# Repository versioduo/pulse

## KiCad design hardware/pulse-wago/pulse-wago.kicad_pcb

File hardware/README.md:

# V2 pulse

🧲 16 Channel Intelligent Solenoid Controller

## Schematic
[PDF](pulse/pulse.pdf)

## Bill Of Materials
[Interactive BOM](https://versioduo.com/view?url=https://raw.githubusercontent.com/versioduo/pulse/refs/heads/main/hardware/pulse/pulse-bom.html)

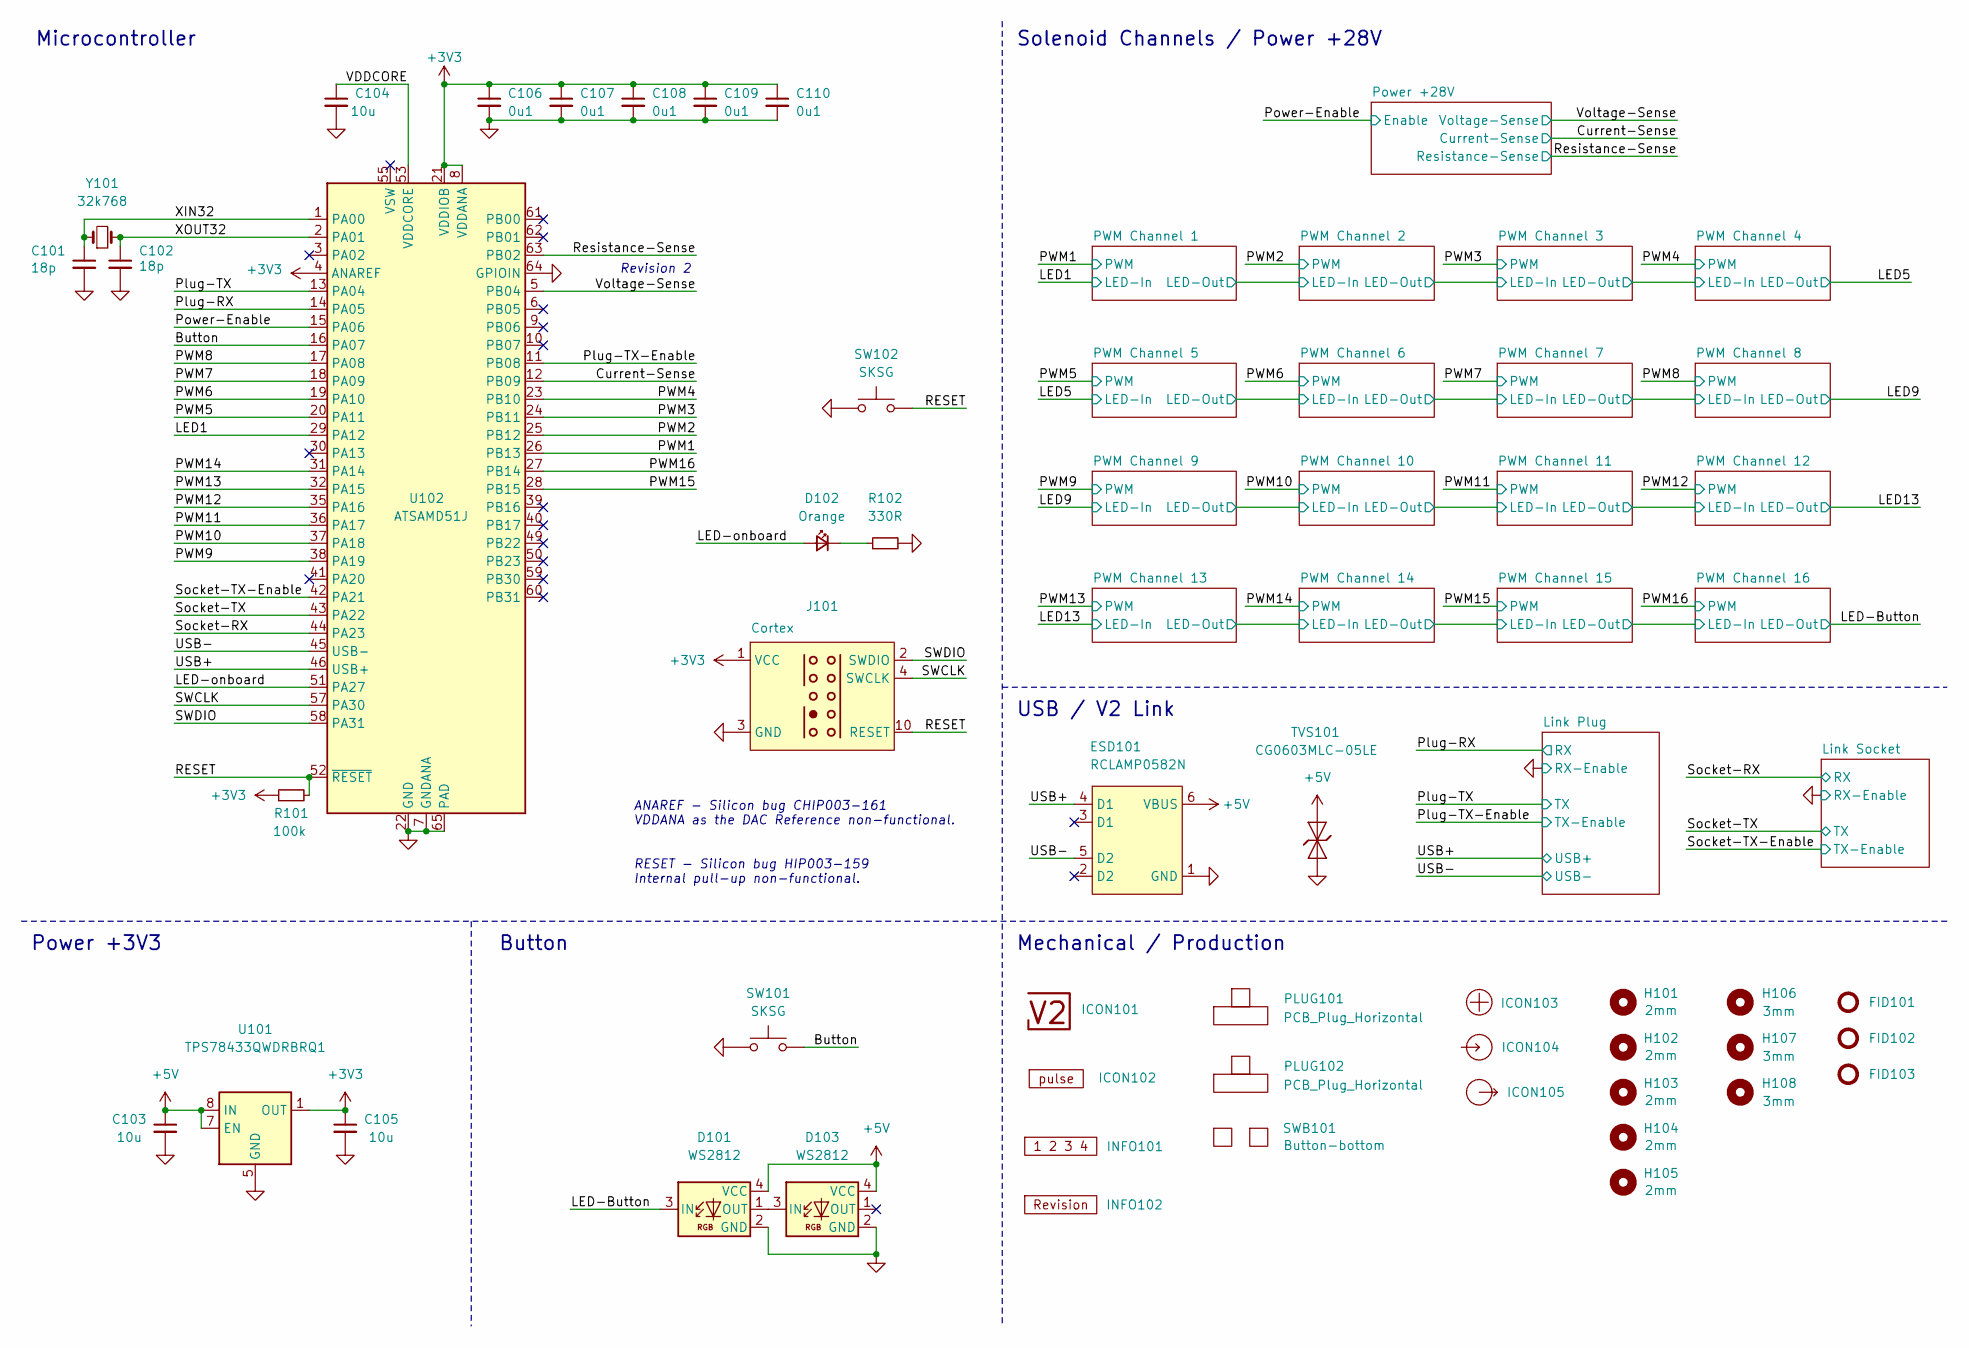
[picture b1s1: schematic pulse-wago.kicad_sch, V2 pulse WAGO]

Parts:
C101, C102: 18p; C_1608; Rating 50V; Mouser 810-CGA3E2C0G1H180J
C103, C105: 10u; C_2012; Rating 25V; Mouser 810-C2012X5R1E106K
C104: 10u; C_1608; Rating 10V; Mouser 810-C1608X6S1A106M
C106, C107, C108, C109, C110: 0u1; C_1608; Rating 50V; Mouser 810-CGA3E2X7R1H104MA
D101, D103: WS2812; WS2812-2020; Rating 15mA; LCSC C965555
D102: Orange; LED_1608; Rating 605nm; Mouser 755-SML-D12D1WT86
ESD101: RCLAMP0582N; SLP1210N6; Rating 20kV; Mouser 947-RCLAMP0582N.TCT
FID101, FID102, FID103: Fiducial_Paste; Fiducial_0.5mm_Mask1mm_Paste
H101, H102, H103, H104, H105: 2mm; MountingHole_2mm
H106, H107, H108: 3mm; MountingHole_3mm
ICON101: V2-logo; Logo_Small
ICON102: Board_pulse; Board_pulse_Small
ICON103: Plus; Plus_Small
ICON104: Arrow_In
ICON105: Arrow_Out
INFO101: Layer_Numbers-6
INFO102: Revision
J101: Cortex
PLUG101, PLUG102: PCB_Plug_Horizontal
R101: 100k; R_1608; Rating 100mW; Mouser 71-CRCW0603100KFKEAC
R102: 330R; R_1608; Rating 100mW; Mouser 71-CRCW0603330RFKEAC
SW101, SW102: SKSG; Rating 1.6N; Mouser 688-SKSGACE010
SWB101: Button-bottom; PCB_Button-bottom
TVS101: CG0603MLC-05LE; D_1608; Rating 5V; Mouser 652-CG0603MLC-05LE
U101: TPS78433QWDRBRQ1; VSON-8-1_3x3mm_P0.65_EP1.65x2.4mm; Rating 300mA; Mouser 595-TPS78433QWDRBRQ1
U102: ATSAMD51J; QFN-64-1EP_9x9mm_P0.5mm_EP4.8x4.8mm_ThermalVias; Rating Cortex-M4F; Mouser 556-ATSAMD51J19AMU
Y101: 32k768; Crystal_SMD_3215-2Pin_3.2x1.5mm; Rating 10ppm; Mouser 815-ABS0716632.768KT

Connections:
+3V3: C105.1, C106.1, C107.1, C108.1, C109.1, C110.1, J101.1 (VCC), R101.1, U101.1 (OUT), U102.4 (ANAREF), U102.8 (VDDANA), U102.21 (VDDIOB), U102.34 (VDDIO), U102.48 (VDDIO), U102.56 (VDDIO); also elsewhere on the board
+5V: C103.1, D101.4 (VCC), D103.4 (VCC), ESD101.6 (VBUS), TVS101.2 (A), U101.6 (EN), U101.7 (EN), U101.8 (IN); also elsewhere on the board
/Button: SW101.2, U102.16 (PA07)
/Current-Sense: U102.12 (PB09); also elsewhere on the board
/LED1: U102.29 (PA12); also elsewhere on the board
/LED-Button: D101.3 (IN); also elsewhere on the board
/LED-onboard: D102.2 (A), U102.51 (PA27)
/PWM1: U102.26 (PB13); also elsewhere on the board
/PWM2: U102.25 (PB12); also elsewhere on the board
/PWM3: U102.24 (PB11); also elsewhere on the board
/PWM4: U102.23 (PB10); also elsewhere on the board
/PWM5: U102.20 (PA11); also elsewhere on the board
/PWM6: U102.19 (PA10); also elsewhere on the board
/PWM7: U102.18 (PA09); also elsewhere on the board
/PWM8: U102.17 (PA08); also elsewhere on the board
/PWM9: U102.38 (PA19); also elsewhere on the board
/PWM10: U102.37 (PA18); also elsewhere on the board
/PWM11: U102.36 (PA17); also elsewhere on the board
/PWM12: U102.35 (PA16); also elsewhere on the board
/PWM13: U102.32 (PA15); also elsewhere on the board
/PWM14: U102.31 (PA14); also elsewhere on the board
/PWM15: U102.28 (PB15); also elsewhere on the board
/PWM16: U102.27 (PB14); also elsewhere on the board
/Plug-RX: U102.14 (PA05); also elsewhere on the board
/Plug-TX: U102.13 (PA04); also elsewhere on the board
/Plug-TX-Enable: U102.11 (PB08); also elsewhere on the board
/Power-Enable: U102.15 (PA06); also elsewhere on the board
/RESET: J101.10 (RESET), R101.2, SW102.2, U102.52 (~RESET)
/Resistance-Sense: U102.63 (PB02); also elsewhere on the board
/SWCLK: J101.4 (SWCLK), U102.57 (PA30)
/SWDIO: J101.2 (SWDIO), U102.58 (PA31)
/Socket-RX: U102.44 (PA23); also elsewhere on the board
/Socket-TX: U102.43 (PA22); also elsewhere on the board
/Socket-TX-Enable: U102.42 (PA21); also elsewhere on the board
/USB+: ESD101.4 (D1), U102.46 (USB+); also elsewhere on the board
/USB-: ESD101.5 (D2), U102.45 (USB-); also elsewhere on the board
/VDDCORE: C104.1, U102.53 (VDDCORE)
/Voltage-Sense: U102.5 (PB04); also elsewhere on the board
/XIN32: C101.1, U102.1 (PA00), Y101.1
/XOUT32: C102.1, U102.2 (PA01), Y101.2
GND: C101.2, C102.2, C103.2, C104.2, C105.2, C106.2, C107.2, C108.2, C109.2, C110.2, D101.2 (GND), D103.2 (GND), ESD101.1 (GND), J101.3 (GND), J101.5 (GND), R102.2, SW101.1, SW102.1, TVS101.1 (K), U101.5 (GND), U101.9 (GND), U102.7 (GNDANA), U102.22 (GND), U102.33 (GND), U102.47 (GND), U102.54 (GND), U102.64 (GPIOIN), U102.65 (PAD); also elsewhere on the board
unnamed: D101.1 (OUT), D103.3 (IN)
unnamed: D102.1 (K), R102.1

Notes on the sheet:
﻿ANAREF - Silicon bug CHIP003-161 VDDANA as the DAC Reference non-functional.
Solenoid Channels / Power +28V
RESET - ﻿Silicon bug HIP003-159 Internal pull-up non-functional.
Button
Revision 2
USB / V2 Link
Mechanical / Production
Power +3V3
Microcontroller

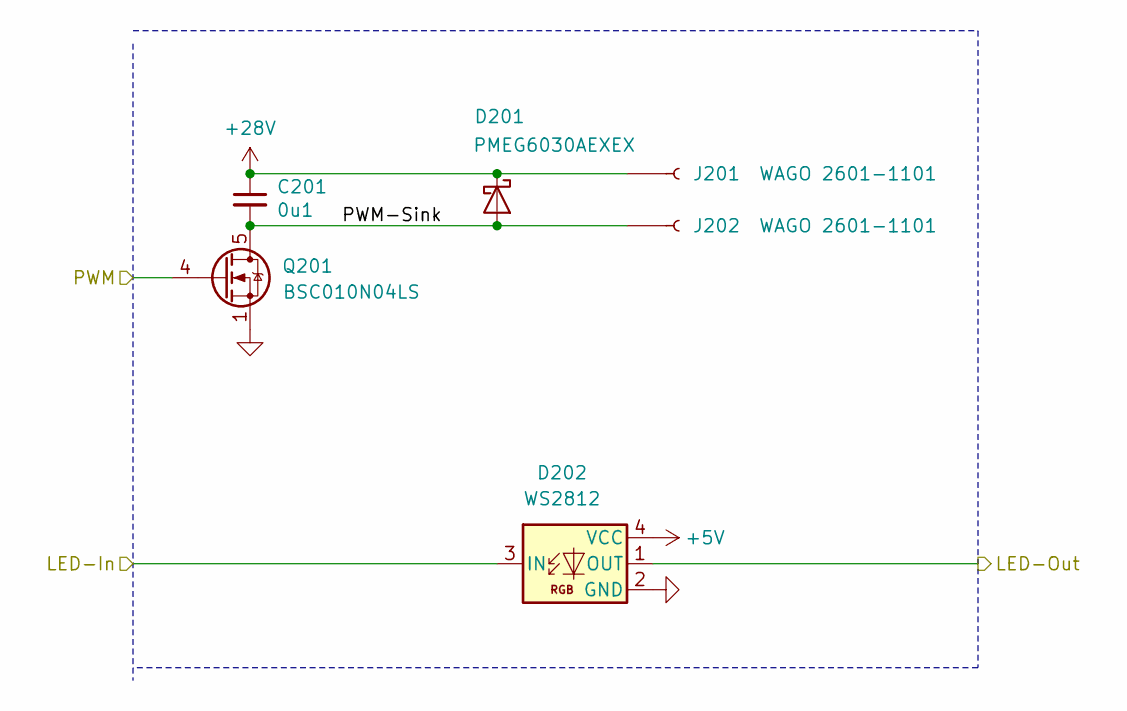
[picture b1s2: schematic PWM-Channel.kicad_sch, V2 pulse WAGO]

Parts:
C201: 0u1; C_1608; Rating 50V; Mouser 810-CGA3E2X7R1H104MA
D201: PMEG6030AEXEX; D_SOD-123HP; Rating 60V; Mouser 771-PMEG6030AEXEX
D202: WS2812; WS2812-2020; Rating 15mA; LCSC C965555
J201, J202: WAGO 2601-1101; 2601-1101; Rating 17.5A
Q201: BSC010N04LS; TDSON-8-FL; Rating 40V; Mouser 726-BSC010N04LS

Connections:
+5V: D202.4 (VCC); also elsewhere on the board
+28V: C201.1, D201.1 (K), J201.1; also elsewhere on the board
/LED1: D202.3 (IN); also elsewhere on the board
/PWM1: Q201.4 (G); also elsewhere on the board
/PWM Channel 1/LED-Out: D202.1 (OUT); also elsewhere on the board
/PWM Channel 1/PWM-Sink: C201.2, D201.2 (A), J202.1, Q201.5 (D)
GND: D202.2 (GND), Q201.1 (S); also elsewhere on the board

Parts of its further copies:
C301, C401, C501, C601, C701, C801, C901, C1001, C1101, C1201, C1301, C1401, C1501, C1601, C1701: 0u1; C_1608; Rating 50V; Mouser 810-CGA3E2X7R1H104MA
D301, D401, D501, D601, D701, D801, D901, D1001, D1101, D1201, D1301, D1401, D1501, D1601, D1701: PMEG6030AEXEX; D_SOD-123HP; Rating 60V; Mouser 771-PMEG6030AEXEX
D302, D402, D502, D602, D702, D802, D902, D1002, D1102, D1202, D1302, D1402, D1502, D1602, D1702: WS2812; WS2812-2020; Rating 15mA; LCSC C965555
J301, J302, J401, J402, J501, J502, J601, J602, J701, J702, J801, J802, J901, J902, J1001, J1002, J1101, J1102, J1201, J1202, J1301, J1302, J1401, J1402, J1501, J1502, J1601, J1602, J1701, J1702: WAGO 2601-1101; 2601-1101; Rating 17.5A
Q301, Q401, Q501, Q601, Q701, Q801, Q901, Q1001, Q1101, Q1201, Q1301, Q1401, Q1501, Q1601, Q1701: BSC010N04LS; TDSON-8-FL; Rating 40V; Mouser 726-BSC010N04LS

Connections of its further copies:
+5V: D302.4 (VCC), D402.4 (VCC), D502.4 (VCC), D602.4 (VCC), D702.4 (VCC), D802.4 (VCC), D902.4 (VCC), D1002.4 (VCC), D1102.4 (VCC), D1202.4 (VCC), D1302.4 (VCC), D1402.4 (VCC), D1502.4 (VCC), D1602.4 (VCC), D1702.4 (VCC); also elsewhere on the board
+28V: C301.1, C401.1, C501.1, C601.1, C701.1, C801.1, C901.1, C1001.1, C1101.1, C1201.1, C1301.1, C1401.1, C1501.1, C1601.1, C1701.1, D301.1 (K), D401.1 (K), D501.1 (K), D601.1 (K), D701.1 (K), D801.1 (K), D901.1 (K), D1001.1 (K), D1101.1 (K), D1201.1 (K), D1301.1 (K), D1401.1 (K), D1501.1 (K), D1601.1 (K), D1701.1 (K), J301.1, J401.1, J501.1, J601.1, J701.1, J801.1, J901.1, J1001.1, J1101.1, J1201.1, J1301.1, J1401.1, J1501.1, J1601.1, J1701.1; also elsewhere on the board
/LED5: D502.1 (OUT), D602.3 (IN)
/LED9: D902.1 (OUT), D1002.3 (IN)
/LED13: D1302.1 (OUT), D1402.3 (IN)
/LED-Button: D1702.1 (OUT); also elsewhere on the board
/PWM2: Q301.4 (G); also elsewhere on the board
/PWM3: Q401.4 (G); also elsewhere on the board
/PWM4: Q501.4 (G); also elsewhere on the board
/PWM5: Q601.4 (G); also elsewhere on the board
/PWM6: Q701.4 (G); also elsewhere on the board
/PWM7: Q801.4 (G); also elsewhere on the board
/PWM8: Q901.4 (G); also elsewhere on the board
/PWM9: Q1001.4 (G); also elsewhere on the board
/PWM10: Q1101.4 (G); also elsewhere on the board
/PWM11: Q1201.4 (G); also elsewhere on the board
/PWM12: Q1301.4 (G); also elsewhere on the board
/PWM13: Q1401.4 (G); also elsewhere on the board
/PWM14: Q1501.4 (G); also elsewhere on the board
/PWM15: Q1601.4 (G); also elsewhere on the board
/PWM16: Q1701.4 (G); also elsewhere on the board
/PWM Channel 1/LED-Out: D302.3 (IN); also elsewhere on the board
/PWM Channel 2/LED-Out: D302.1 (OUT), D402.3 (IN)
/PWM Channel 2/PWM-Sink: C301.2, D301.2 (A), J302.1, Q301.5 (D)
/PWM Channel 3/LED-Out: D402.1 (OUT), D502.3 (IN)
/PWM Channel 3/PWM-Sink: C401.2, D401.2 (A), J402.1, Q401.5 (D)
/PWM Channel 4/PWM-Sink: C501.2, D501.2 (A), J502.1, Q501.5 (D)
/PWM Channel 5/LED-Out: D602.1 (OUT), D702.3 (IN)
/PWM Channel 5/PWM-Sink: C601.2, D601.2 (A), J602.1, Q601.5 (D)
/PWM Channel 6/LED-Out: D702.1 (OUT), D802.3 (IN)
/PWM Channel 6/PWM-Sink: C701.2, D701.2 (A), J702.1, Q701.5 (D)
/PWM Channel 7/LED-Out: D802.1 (OUT), D902.3 (IN)
/PWM Channel 7/PWM-Sink: C801.2, D801.2 (A), J802.1, Q801.5 (D)
/PWM Channel 8/PWM-Sink: C901.2, D901.2 (A), J902.1, Q901.5 (D)
/PWM Channel 9/PWM-Sink: C1001.2, D1001.2 (A), J1002.1, Q1001.5 (D)
/PWM Channel 10/LED-In: D1002.1 (OUT), D1102.3 (IN)
/PWM Channel 10/LED-Out: D1102.1 (OUT), D1202.3 (IN)
/PWM Channel 10/PWM-Sink: C1101.2, D1101.2 (A), J1102.1, Q1101.5 (D)
/PWM Channel 11/LED-Out: D1202.1 (OUT), D1302.3 (IN)
/PWM Channel 11/PWM-Sink: C1201.2, D1201.2 (A), J1202.1, Q1201.5 (D)
/PWM Channel 12/PWM-Sink: C1301.2, D1301.2 (A), J1302.1, Q1301.5 (D)
/PWM Channel 13/LED-Out: D1402.1 (OUT), D1502.3 (IN)
/PWM Channel 13/PWM-Sink: C1401.2, D1401.2 (A), J1402.1, Q1401.5 (D)
/PWM Channel 14/LED-Out: D1502.1 (OUT), D1602.3 (IN)
/PWM Channel 14/PWM-Sink: C1501.2, D1501.2 (A), J1502.1, Q1501.5 (D)
/PWM Channel 15/LED-Out: D1602.1 (OUT), D1702.3 (IN)
/PWM Channel 15/PWM-Sink: C1601.2, D1601.2 (A), J1602.1, Q1601.5 (D)
/PWM Channel 16/PWM-Sink: C1701.2, D1701.2 (A), J1702.1, Q1701.5 (D)
GND: D302.2 (GND), D402.2 (GND), D502.2 (GND), D602.2 (GND), D702.2 (GND), D802.2 (GND), D902.2 (GND), D1002.2 (GND), D1102.2 (GND), D1202.2 (GND), D1302.2 (GND), D1402.2 (GND), D1502.2 (GND), D1602.2 (GND), D1702.2 (GND), Q301.1 (S), Q401.1 (S), Q501.1 (S), Q601.1 (S), Q701.1 (S), Q801.1 (S), Q901.1 (S), Q1001.1 (S), Q1101.1 (S), Q1201.1 (S), Q1301.1 (S), Q1401.1 (S), Q1501.1 (S), Q1601.1 (S), Q1701.1 (S); also elsewhere on the board

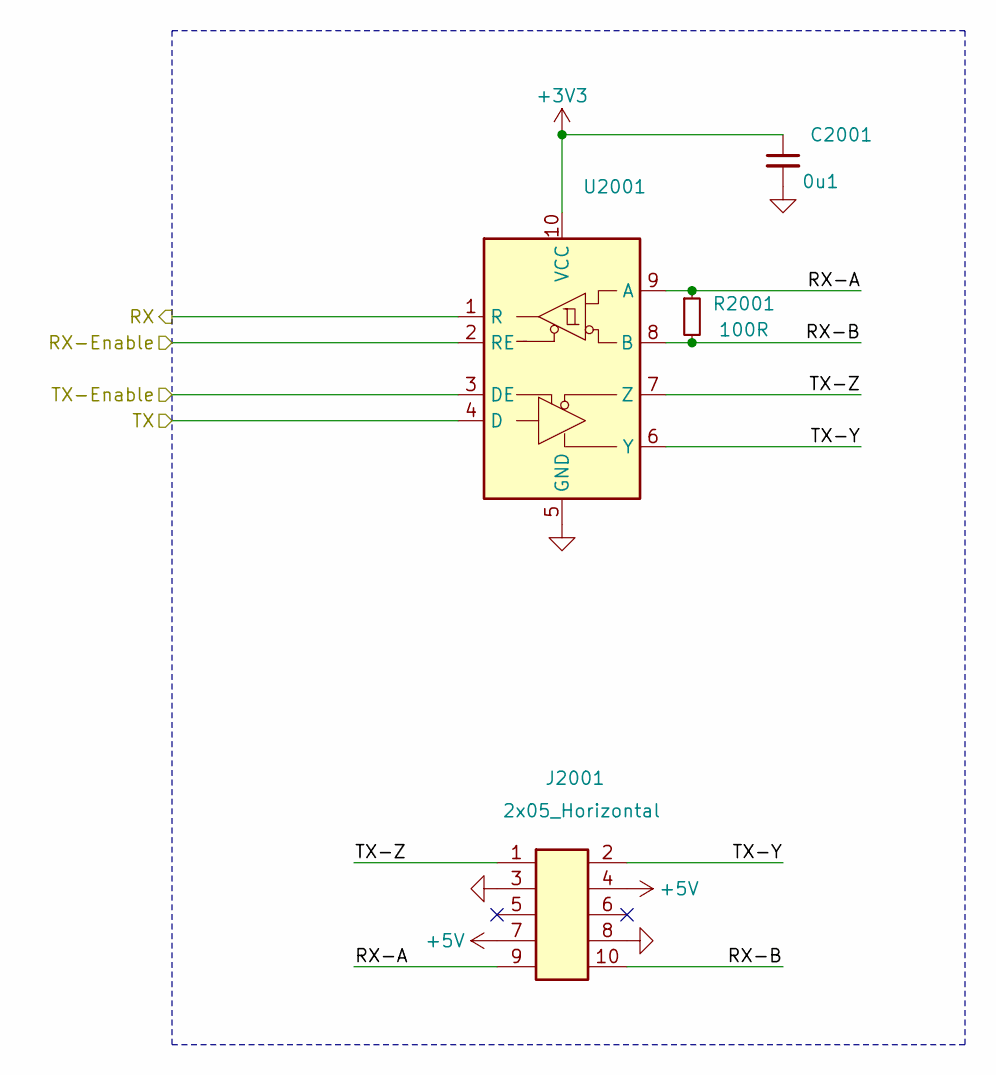
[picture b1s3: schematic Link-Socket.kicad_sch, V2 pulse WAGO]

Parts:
C2001: 0u1; C_1608; Rating 50V; Mouser 810-CGA3E2X7R1H104MA
J2001: 2x05_Horizontal; PinHeader_2x05_P1.27mm_Horizontal; Rating 1A; Mouser 649-200211120001T4LF
R2001: 100R; R_1608; Rating 330mW; Mouser 71-CRCW0603100RFKEAH
U2001: VSON-10-4-1EP_3x3mm_P0.5mm_EP1.65x2.4mm_ThermalVias

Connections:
+3V3: C2001.1, U2001.10 (VCC); also elsewhere on the board
+5V: J2001.4, J2001.7; also elsewhere on the board
/Link Socket/RX-A: J2001.9, R2001.1, U2001.9 (A)
/Link Socket/RX-B: J2001.10, R2001.2, U2001.8 (B)
/Link Socket/TX-Y: J2001.2, U2001.6 (Y)
/Link Socket/TX-Z: J2001.1, U2001.7 (Z)
/Socket-RX: U2001.1 (R); also elsewhere on the board
/Socket-TX: U2001.4 (D); also elsewhere on the board
/Socket-TX-Enable: U2001.3 (DE); also elsewhere on the board
GND: C2001.2, J2001.3, J2001.8, U2001.2 (RE), U2001.5 (GND), U2001.11 (GND); also elsewhere on the board

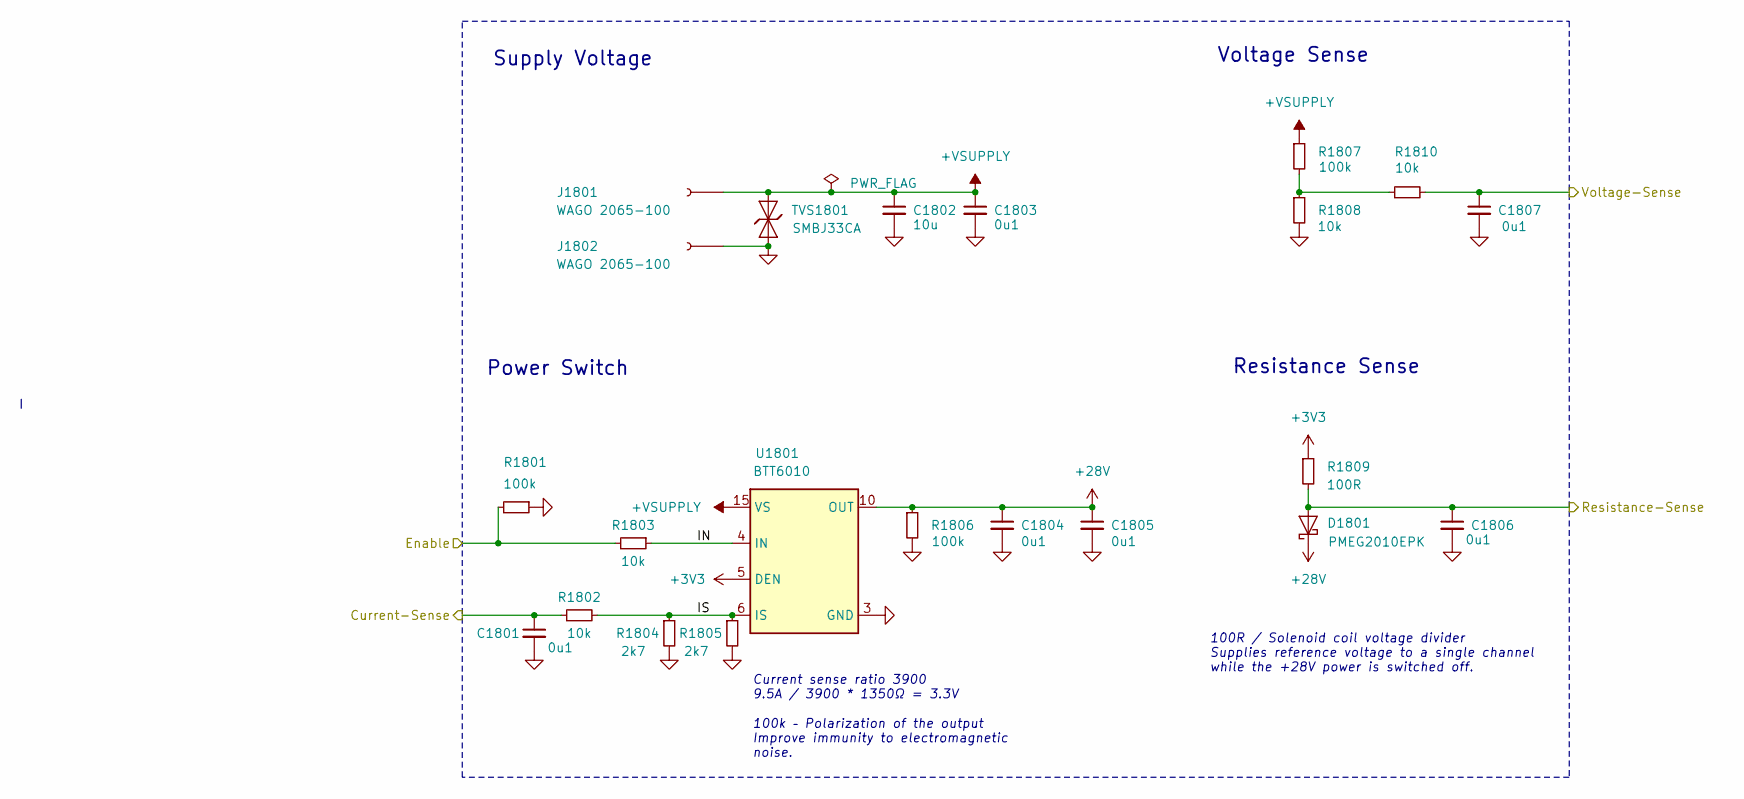
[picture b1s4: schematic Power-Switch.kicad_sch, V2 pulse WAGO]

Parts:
C1801, C1803, C1804, C1805, C1806, C1807: 0u1; C_1608; Rating 50V; Mouser 810-CGA3E2X7R1H104MA
C1802: 10u; C_3225; Rating 50V; Mouser 810-CNC6P1X7R1H106K2
D1801: PMEG2010EPK; D_SOD-1608; Rating 20V; Mouser 771-PMEG2010EPK
J1801, J1802: WAGO 2065-100; 2065-100; Rating 9A
R1801, R1806, R1807: 100k; R_1608; Rating 100mW; Mouser 71-CRCW0603100KFKEAC
R1802, R1803, R1808, R1810: 10k; R_1608; Rating 100mW; Mouser 71-CRCW060310K0FKEAC
R1804, R1805: 2k7; R_1608; Rating 100mW; Mouser 71-CRCW06032K70FKEAC
R1809: 100R; R_1608; Rating 330mW; Mouser 71-CRCW0603100RFKEAH
TVS1801: SMBJ33CA; D_SMB; Rating 33V; Mouser 652-SMBJ33CA-Q
U1801: BTT6010; PG-TDS0-14; Rating 36V; Mouser 726-BTT60101ERBXUMA1

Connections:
+3V3: R1809.1, U1801.5 (DEN); also elsewhere on the board
+28V: C1804.1, C1805.1, D1801.1 (K), R1806.1, U1801.10 (OUT), U1801.11 (OUT), U1801.12 (OUT); also elsewhere on the board
/Current-Sense: C1801.1, R1802.1; also elsewhere on the board
/Power +28V/+VSUPPLY: C1802.1, C1803.1, J1801.1, R1807.1, TVS1801.2 (A), U1801.15 (VS)
/Power +28V/IN: R1803.1, U1801.4 (IN)
/Power +28V/IS: R1802.2, R1804.1, R1805.1, U1801.6 (IS)
/Power-Enable: R1801.2, R1803.2; also elsewhere on the board
/Resistance-Sense: C1806.1, D1801.2 (A), R1809.2; also elsewhere on the board
/Voltage-Sense: C1807.1, R1810.2; also elsewhere on the board
GND: C1801.2, C1802.2, C1803.2, C1804.2, C1805.2, C1806.2, C1807.2, J1802.1, R1801.1, R1804.2, R1805.2, R1806.2, R1808.2, TVS1801.1 (K), U1801.3 (GND); also elsewhere on the board
unnamed: R1807.2, R1808.1, R1810.1

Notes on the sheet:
Supply Voltage
100k – Polarization of the output Improve immunity to electromagnetic noise.
Current sense ratio 3900 9.5A / 3900 * 1350Ω = 3.3V
Voltage Sense
Power Switch
100R / Solenoid coil voltage divider Supplies reference voltage to a single channel while the +28V power is switched off.
Resistance Sense

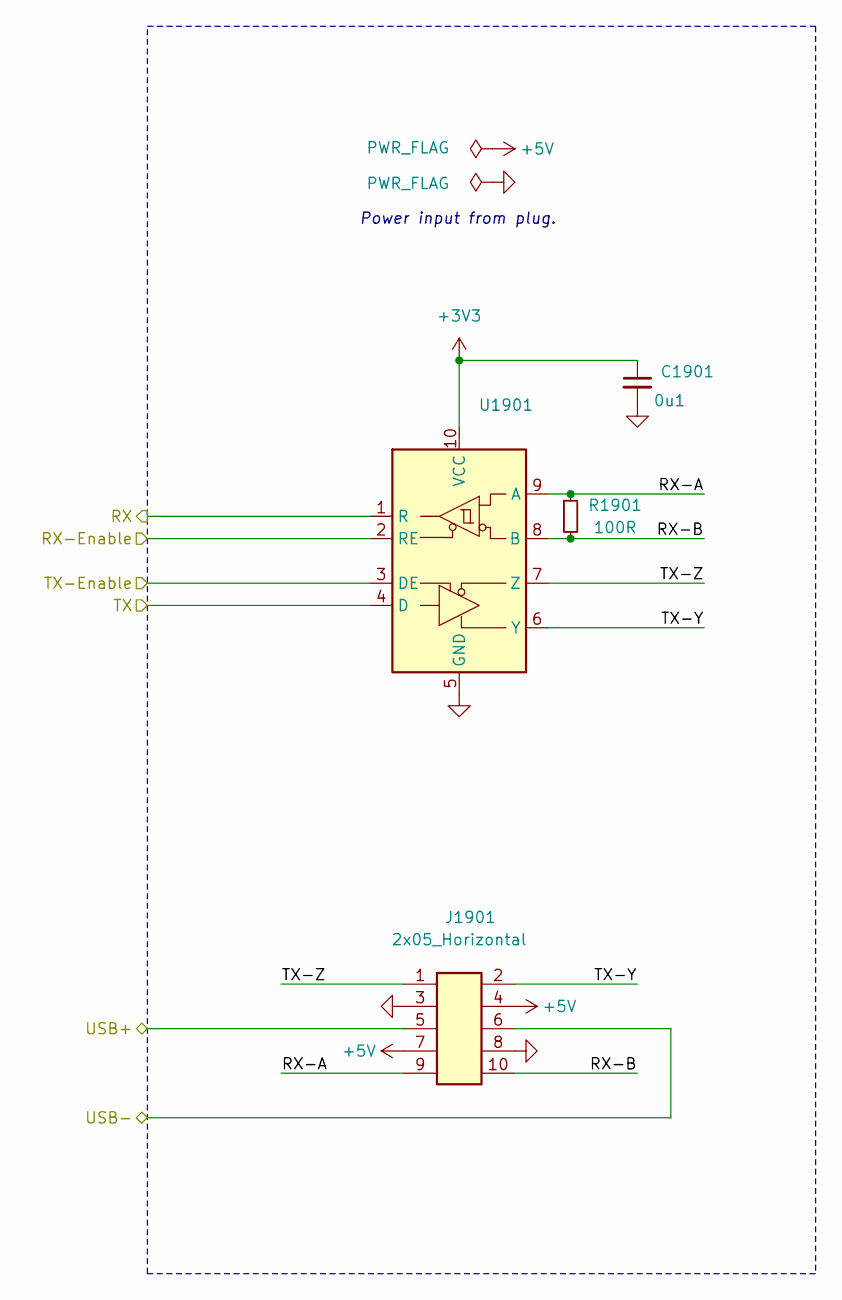
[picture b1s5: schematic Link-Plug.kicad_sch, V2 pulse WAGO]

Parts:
C1901: 0u1; C_1608; Rating 50V; Mouser 810-CGA3E2X7R1H104MA
J1901: 2x05_Horizontal; PinHeader_2x05_P1.27mm_Horizontal; Rating 1A; Mouser 649-200211120001T4LF
R1901: 100R; R_1608; Rating 330mW; Mouser 71-CRCW0603100RFKEAH
U1901: VSON-10-4-1EP_3x3mm_P0.5mm_EP1.65x2.4mm_ThermalVias

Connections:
+3V3: C1901.1, U1901.10 (VCC); also elsewhere on the board
+5V: J1901.4, J1901.7; also elsewhere on the board
/Link Plug/RX-A: J1901.9, R1901.1, U1901.9 (A)
/Link Plug/RX-B: J1901.10, R1901.2, U1901.8 (B)
/Link Plug/TX-Y: J1901.2, U1901.6 (Y)
/Link Plug/TX-Z: J1901.1, U1901.7 (Z)
/Plug-RX: U1901.1 (R); also elsewhere on the board
/Plug-TX: U1901.4 (D); also elsewhere on the board
/Plug-TX-Enable: U1901.3 (DE); also elsewhere on the board
/USB+: J1901.5; also elsewhere on the board
/USB-: J1901.6; also elsewhere on the board
GND: C1901.2, J1901.3, J1901.8, U1901.2 (RE), U1901.5 (GND), U1901.11 (GND); also elsewhere on the board

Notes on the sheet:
Power input from plug.

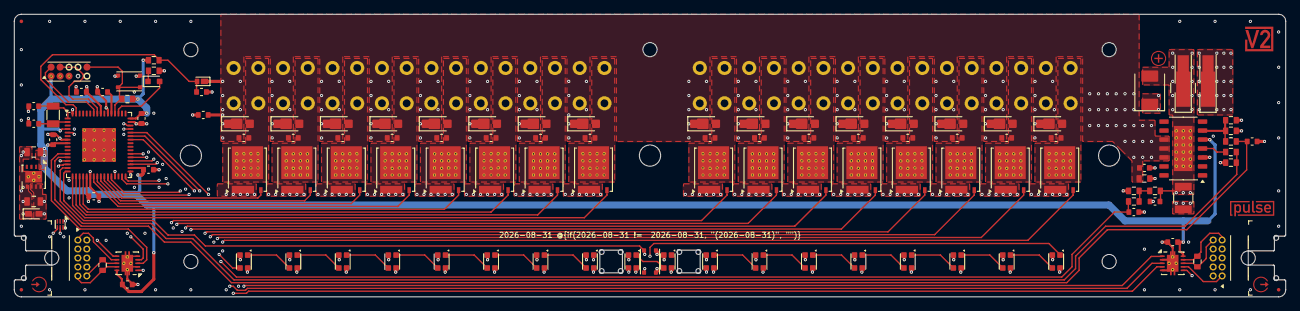
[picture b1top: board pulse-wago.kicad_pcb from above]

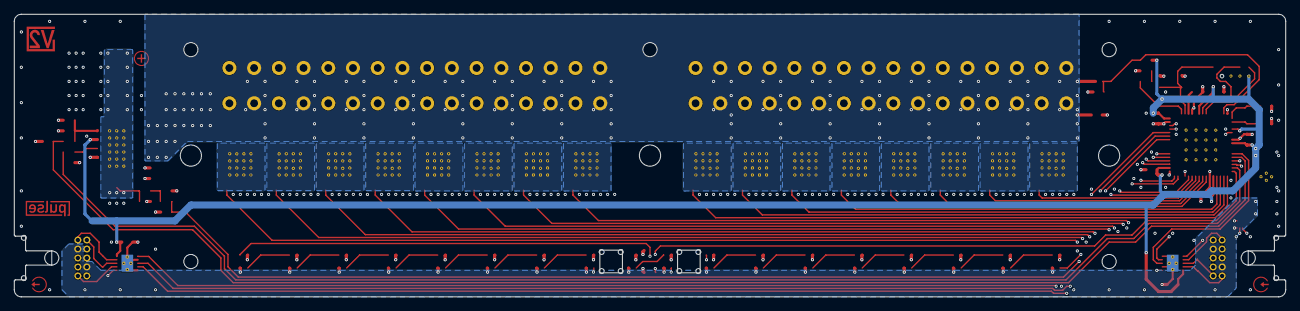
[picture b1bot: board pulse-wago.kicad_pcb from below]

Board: 6 copper layers, 180.0 x 40.0 mm, 170 parts (32 on the bottom side), 87 nets.

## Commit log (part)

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2025-12-29 Import
2025-12-29 Colour
2026-01-14 Update parts
2026-01-26 Refresh
2026-02-01 Update library
2026-02-10 Use date as revision
2026-02-13 Replace Order_Number
2026-03-11 Update back
2026-03-11 Replace diode
2026-03-12 Update sheet metal
2026-03-14 Update ESD suppressor
2026-05-11 Good Bye Imperial
2026-06-08 Switch to 6 layer
2026-06-21 Update MIDI API
2026-06-23 Update V2MIDI API
